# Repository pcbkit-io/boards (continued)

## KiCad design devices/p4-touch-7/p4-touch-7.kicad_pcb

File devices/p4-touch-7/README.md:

# p4-touch-7 — a 7" ESP32-P4 touch screen running NucleoOS

A board for [NucleoOS-P4](https://github.com/indecenti/NucleoOS-P4) (by indecenti): the
Guition JC1060P470C's circuit (its published schematic) at NucleoOS's own pin map, laid out by
PCBKit behind a 7" 1024 × 600 MIPI-DSI touch panel. In the app it runs NucleoOS's own release,
unmodified: the factory image from its GitHub release, booted by Espressif's ESP32-P4 boot ROM on
PCBKit's model of the chip, the card in the microSD socket holding the release's SD-card archive.

| | |
|---|---|
| Processor | ESP32-P4NRW32 (two RISC-V cores at 360 MHz, 32 MB PSRAM in package), W25Q128JV 16 MB flash, 40 MHz crystal |
| Screen | JC1060M070N-I: 7" 1024 × 600 IPS, JD9165 over 2-lane MIPI-DSI (FPC1, 30 pins), GT911 capacitive touch on I2C0 (FPC2, 6 pins); its AVDD from an MT3608, VGH and VGL from charge pumps, the backlight from a second MT3608 dimmed by LEDC (an 18 V zener into its FB holds the output near 19 V with the panel unplugged, under the 30 V its switch pin takes) |
| Radio | ESP32-C6-MINI-1 on the P4's second SD/MMC slot (ESP-Hosted), its antenna over the top edge |
| Audio | ES8311 codec (electret microphone in, PAM8403 to a speaker connector) on I2S0 and I2C0 |
| Storage | microSD socket on SD/MMC slot 0 (GPIO39–44, 4-bit) |
| Clock | DS3231 with a CR2032 |
| USB | three USB-C: the console (CH340C, auto-reset into the boot loader), the P4's full-speed and high-speed ports (the last one a Type-C host: 56 kΩ Rp on CC, 5 V to what is plugged in through an SY6280 switch limited to 750 mA) |
| Power | a Li-ion cell on IP5306 (charger and 5 V boost, its key the power button), SY8089 bucks to 3.3 V and to the P4's 1.2 V core supply |
| Board | 160 × 96 mm, 6 layers (JLCPCB JLC06161H-3313, controlled impedance), four M3 holes onto the panel's standoffs |

<!-- STATUS -->
**Board status** (measured on the dev host with PCBKit's CLI): `pcbkit check`: complete — 0 errors,
23 warnings (the DSI and USB pairs' coupling, impedance and skew where they leave the P4's 0.35 mm
pins, 13 narrower tracks in a class, two rail names, two VSYS stubs the router leaves), 0 unrouted
nets. 179 components, 118 nets, 2644 track segments (6155 mm), 596 vias.
`analysis.run { lens: "ready" }`: 12 to fix (decoupling capacitors 3–4 mm from their P4 supply pins,
under the chip on the back) and 24 to consider.
Every assembled line has its LCSC code (chosen by stock at JLCPCB, 2026-10-25); `pcbkit export
--format fab` succeeds without `--force`. **Two parts are out of stock at JLCPCB**: the ESP32-P4NRW32
(no ESP32-P4 of any revision is; send it as a consigned part) and the 4.2 x 3.2 mm BOOT and RESET
buttons (PTS810, or any 4.2 x 3.2 mm tact switch). The ESP32-C6 is the MINI-1-H4 (the N4's 105 °C
twin, same pins).
<!-- /STATUS -->

## Run it in the browser

Open the board and press **Run**: the page fetches NucleoOS's release (its factory image and its
SD-card archive, from GitHub, checked against the SHA-256 this design declares) and Espressif's ROM,
and runs them. NucleoOS boots to its setup wizard; touch the screen in 3D to go through it to the
launcher.

What does not run, as NucleoOS itself reports it:

- **No radio.** The ESP32-C6 is on the board but held in reset: its own firmware (ESP-Hosted) does
  not run here, so NucleoOS finds no Wi-Fi ("This board has no Wi-Fi radio") and no Bluetooth.
  Nothing pretends to be a network.
- **The RTC.** NucleoOS looks for an RX8130 at 0x14; this board (like Guition's, which fits an
  RX-8025T) has a DS3231 at 0x68, so the clock starts unset.
- The PPA's blender and YUV modes, the JPEG codec and the camera are not modelled yet: an app that
  uses them stops the device and says which block.

## Order, flash

1. Order with assembly (`pcbkit export --format fab`); the panel plugs into FPC1 and FPC2.
2. Flash NucleoOS's factory image over the console port: `esptool.py --chip esp32p4 write_flash 0
   nucleoos-p4-1.2.189-jc1060p470c-factory.bin` (the CH340C's DTR and RTS put the P4 into its boot
   loader); unzip `nucleoos-p4-sdcard.zip` onto a FAT32 microSD card.

NucleoOS's chip revision: its v1.2.x images are built for ESP32-P4 revision v1.x (the image says
"max chip rev v1.99"); new ESP32-P4NRW32X parts are revision v3 and need an image built for it.

Licence: the board CC0 1.0; NucleoOS is the PolyForm Noncommercial License 1.0.0, fetched from its
own release and never copied here.

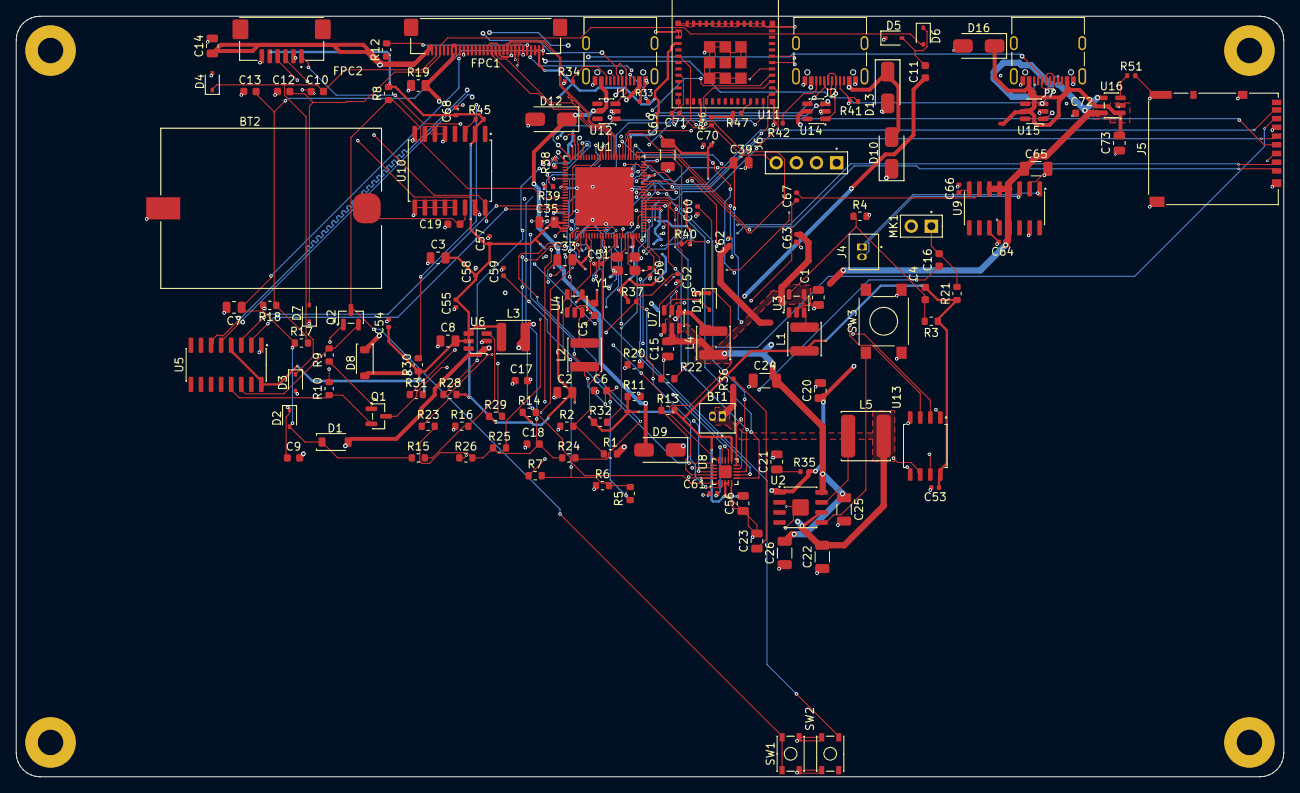
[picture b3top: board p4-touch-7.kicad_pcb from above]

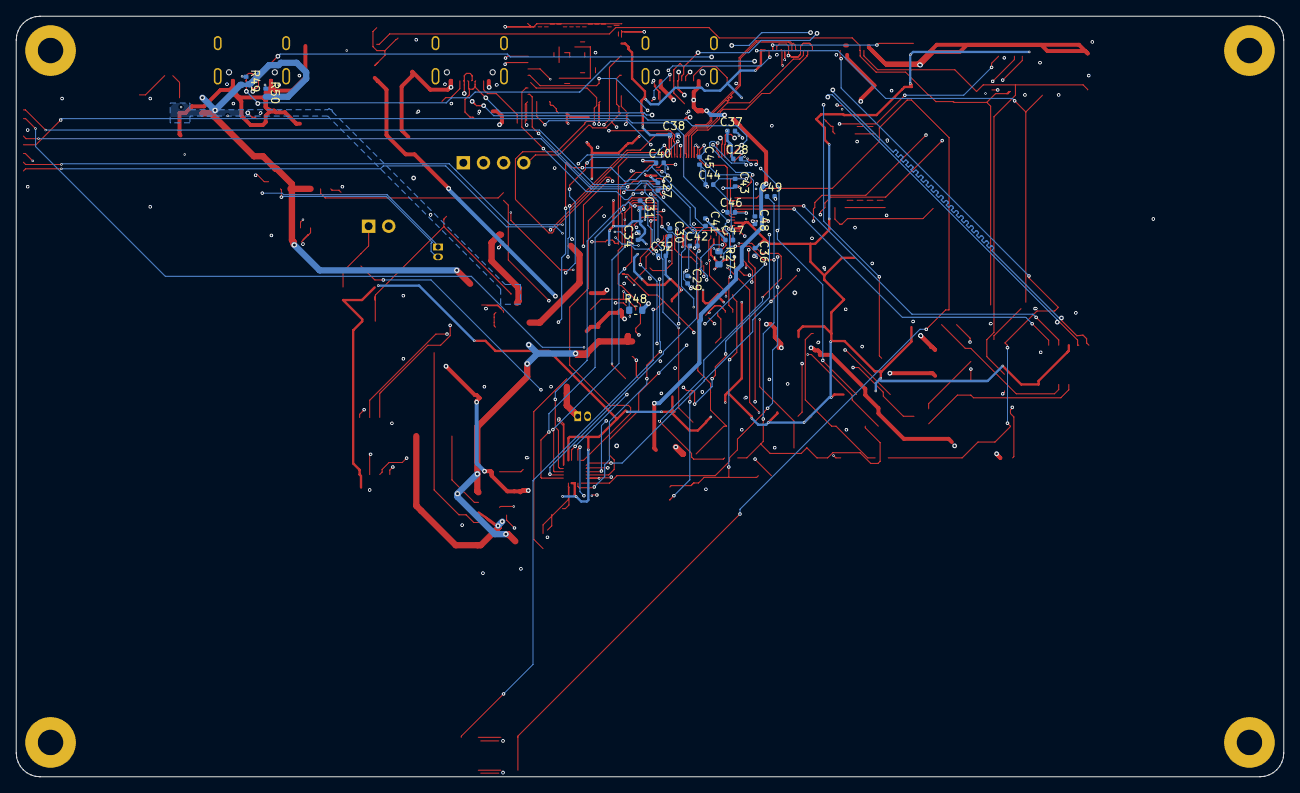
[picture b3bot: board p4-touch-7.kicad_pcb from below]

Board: 6 copper layers, 160.0 x 96.0 mm, 179 parts (25 on the bottom side), 116 nets.

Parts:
BT1: MX1.25-2P; Conn_WireToBoard_1x02_P1.25mm_THT_Vertical
BT2: BS-08-B2AA001; BatteryHolder_MYOUNG_BS-08_CR2032_SMD
C1, C2, C3: 22uF; C_0805_2012Metric
C4: 22pF; C_0603_1608Metric
C5, C6, C18: 10uF; C_0603_1608Metric
C7, C8, C15, C20, C21, C23, C33, C35, C39, C56, C73: 10uF; C_0805_2012Metric
C9, C11, C19: 100nF; C_0603_1608Metric
C10, C12, C13, C16, C17, C72: 1uF; C_0603_1608Metric
C14: 4.7uF; C_0805_2012Metric
C22, C24, C25, C26, C65, C69: 22uF; C_1206_3216Metric
C27, C28, C29, C30, C31, C32, C34, C36, C37, C38, C40, C41, C42, C43, C44, C45, C53, C54, C55, C57, C68, C70: 100nF; C_0402_1005Metric
C46, C47, C48, C49, C52, C58, C59, C60, C61, C62, C63, C64, C66, C71: 1uF; C_0402_1005Metric
C50, C51: 15pF; C_0402_1005Metric
C67: 470nF; C_0402_1005Metric
D1, D8: schottky; D_SOD-123
D2, D3, D5, D6: schottky; D_SOD-323
D4, D15: zener 18V; D_SOD-323
D7: zener 6.8V; D_SOD-323
D9, D10: schottky; D_SMA
D12, D13, D16: tvs 5V; D_SMA
FPC1: FH12-30S-0.5SH(55); Conn_FFC-FPC_1x30_P0.50mm_Horizontal
FPC2: FH12-6S-1SH(55); Conn_FFC-FPC_1x06_P1.00mm_Horizontal
H1, H2, H3, H4: MountingHole_3.2mm_M3_Pad
J1, J2, J7: USB4105-GF-A; USB_C_Receptacle_USB2.0_16P
J4: MX1.25-2P; Conn_WireToBoard_1x02_P1.25mm_THT_Vertical
J5: DM3AT-SF-PEJM5; Hirose_DM3AT_microSD_socket_push-push
J6: PinHeader_1x04_P2.54mm_Vertical
L1, L2: 2.2uH; L_Power_4x4mm
L3, L4: 10uH; L_Power_4x4mm
L5: 1uH; L_Power_6x6mm
LCD1: touch-display; JC1060M070N-I
MK1: CMEJ-0627-42-P; PinHeader_1x02_P2.54mm_Vertical
Q1, Q2: MMBT3904-7-F; SOT-23
R1: 68kohm; R_0603_1608Metric
R2, R4: 100kohm; R_0603_1608Metric
R3: 453kohm; R_0603_1608Metric
R5, R6: 499kohm; R_0603_1608Metric
R7: 0uohm; R_0603_1608Metric
R8, R9, R10, R11, R12, R16, R18, R20, R22, R23, R24, R25, R26, R27: 10kohm; R_0603_1608Metric
R13, R14: 5.1kohm; R_0603_1608Metric
R15: 150kohm; R_0603_1608Metric
R17: 15kohm; R_0603_1608Metric
R19: 3.3ohm; R_0805_2012Metric
R21: 2.2kohm; R_0603_1608Metric
R28, R29, R30, R31, R32: 51kohm; R_0603_1608Metric
R33, R34, R41, R42: 5.1kohm; R_0402_1005Metric
R35, R36: 2ohm; R_0402_1005Metric
R37, R40, R45, R46, R47: 10kohm; R_0402_1005Metric
R38, R39: 2kohm; R_0402_1005Metric
R48: 1kohm; R_0603_1608Metric
R49, R50: 56kohm; R_0402_1005Metric
R51: 9.1kohm; R_0402_1005Metric
SW1, SW2: PTS810SJM250SMTR LFS; SW_Tactile_SPST_4.2x3.2mm_SMD
SW3: PTS645SM43SMTR92 LFS; SW_Tactile_SPST_6x6mm_SMD
U1: ESP32-P4NRW32; QFN-104_10x10mm_0.35mm_pitch_7.5mm_exposed_pad
U2: IP5306; SOIC-8-1EP_3.9x4.9mm_P1.27mm_EP2.09x2.09mm
U3, U4: SY8089AAAC; SOT-23-5
U5: CH340C; SOIC-16_3.9x9.9mm_P1.27mm
U6, U7: MT3608; SOT-23-6
U8: ES8311; QFN-20-1EP_3x3mm_P0.4mm_EP1.65x1.65mm
U9: PAM8403DR; SOIC-16_3.9x9.9mm_P1.27mm
U10: DS3231SN#; SOIC-16W_7.5x10.3mm_P1.27mm
U11: ESP32-C6-MINI-1-N4; ESP32-C6-MINI-1_module_13.2x16.6mm_LGA_53_pads
U12, U14, U15: USBLC6-2SC6; SOT-23-6
U13: W25Q128JVSIQ; SOIC-8_5.23x5.28mm_P1.27mm
U16: SY6280AAC; SOT-23-5
Y1: 40MHz 10pF; Crystal_SMD_3225-4Pin

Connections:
AVDD: C7.1 (a), D1.1 (K), D2.2 (A), FPC1.22, R15.2 (b), R17.2 (b)
AVDD_FB: R15.1 (a), R16.1 (a), U6.3 (FB)
BAT_SENSE: R1.2 (b), R2.1 (a), U1.95 (GPIO52)
BL_FB: D15.2 (A), R48.1 (a), U7.3 (FB)
BL_SW: D8.2 (A), L4.1 (a), U7.1 (SW)
BOOT: Q2.3 (C), R8.1 (a), SW1.1 (a), U1.66 (GPIO35)
C6_CLK: U1.19 (GPIO18), U11.25 (IO19)
C6_CMD: R28.2 (b), U1.20 (GPIO19), U11.24 (IO18)
C6_D0: R29.1 (a), U1.15 (GPIO14), U11.26 (IO20)
C6_D1: R30.2 (b), U1.16 (GPIO15), U11.27 (IO21)
C6_D2: R31.2 (b), U1.17 (GPIO16), U11.28 (IO22)
C6_D3: R32.1 (a), U1.18 (GPIO17), U11.29 (IO23)
C6_EN: C71.1 (a), J6.4, R46.1 (a), U1.98 (GPIO54), U11.8 (EN)
C6_IO2: U1.6 (GPIO6), U11.5 (IO2)
C6_RX: J6.3, U11.30 (RXD0)
C6_TX: J6.2, U11.31 (TXD0)
CHIP_PU: C52.1 (a), Q1.3 (C), R37.1 (a), SW2.1 (a), U1.103 (CHIP_PU)
DAC_P: C67.2 (b), U8.12 (OUTP)
DSI_CLK_N: FPC1.13, U1.37 (DSI_CLKN)
DSI_CLK_P: FPC1.14, U1.38 (DSI_CLKP)
DSI_D0_N: FPC1.7, U1.40 (DSI_DATAN0)
DSI_D0_P: FPC1.8, U1.39 (DSI_DATAP0)
DSI_D1_N: FPC1.10, U1.36 (DSI_DATAN1)
DSI_D1_P: FPC1.11, U1.35 (DSI_DATAP1)
DTR: Q1.2 (E), R10.2 (b), U5.13 (DTR_N)
EN_DCDC: U1.79 (EN_DCDC), U4.1 (EN)
FB_DCDC: R7.2 (b), U1.78 (FB_DCDC)
FS_DN: J2.A7 (DN), J2.B7 (DN), U1.52 (GPIO24), U14.3 (IO2)
FS_DP: J2.A6 (DP), J2.B6 (DP), U1.53 (GPIO25), U14.1 (IO1)
GND: BT1.2, BT2.2 (GND), C1.2 (b), C2.2 (b), C3.2 (b), C5.2 (b), C6.2 (b), C7.2 (b), C8.2 (b), C10.2 (b), C12.2 (b), C13.2 (b), C14.2 (b), C15.2 (b), C17.2 (b), C18.2 (b), C19.2 (b), C20.2 (b), C21.2 (b), C22.2 (b), C23.2 (b), C24.2 (b), C25.2 (b), C26.2 (b), C27.2 (b), C28.2 (b), C29.2 (b), C30.2 (b), C31.2 (b), C32.2 (b), C33.2 (b), C34.2 (b), C35.2 (b), C36.2 (b), C37.2 (b), C38.2 (b), C39.2 (b), C40.2 (b), C41.2 (b), C42.2 (b), C43.2 (b), C44.2 (b), C45.2 (b), C46.2 (b), C47.2 (b), C48.2 (b), C49.2 (b), C50.2 (b), C51.2 (b), C52.2 (b), C53.2 (b), C54.2 (b), C55.2 (b), C56.2 (b), C57.2 (b), C58.2 (b), C59.2 (b), C60.2 (b), C61.2 (b), C62.2 (b), C63.2 (b), C64.2 (b), C65.2 (b), C66.2 (b), C68.2 (b), C69.2 (b), C70.2 (b), C71.2 (b), C72.2 (b), C73.2 (b), D4.2 (A), D5.1 (K), D7.1 (K), D12.2 (A), D13.2 (A), D16.2 (A), FPC1.6, FPC1.9, FPC1.12, FPC1.15, FPC1.21, FPC2.6, H1.1, H2.1, H3.1, H4.1, J1.A1 (GND), J1.A12, J1.B1 (GND), J1.B12, J1.S1 (SHIELD), J2.A1 (GND), J2.A12, J2.B1 (GND), J2.B12, J2.S1 (SHIELD), J5.6 (VSS), J5.SH, J6.1, J7.A1 (GND), J7.A12, J7.B1 (GND), J7.B12, J7.S1 (SHIELD), MK1.2, R2.2 (b), R4.2 (b), R6.2 (b), R16.2 (b), R18.2 (b), R19.2 (b), R20.2 (b), R22.2 (b), R33.2 (b), R34.2 (b), R38.2 (b), R39.2 (b), R41.2 (b), R42.2 (b), R51.2 (b), SW1.2 (b), SW2.2 (b), SW3.2 (b), U1.105 (GND), U2.9 (GND), U3.2 (GND), U4.2 (GND), U5.1 (GND), U6.2 (GND), U7.2 (GND), U8.5 (DGND), U8.10 (AGND), U8.20 (CE), U9.2 (PGND), U9.11 (GND), U9.15 (PGND), U10.5 (GND), U10.6 (GND), U10.7 (GND), U10.8 (GND), U10.9 (GND), U10.10 (GND), U10.11 (GND), U10.12 (GND), U10.13 (GND), U11.1 (GND), U11.2 (GND), U11.11 (GND), U11.14 (GND), U11.36 (GND), U11.37 (GND), U11.38 (GND), U11.39 (GND), U11.40 (GND), U11.41 (GND), U11.42 (GND), U11.43 (GND), U11.44 (GND), U11.45 (GND), U11.46 (GND), U11.47 (GND), U11.48 (GND), U11.49 (GND), U11.50 (GND), U11.51 (GND), U11.52 (GND), U11.53 (GND), U12.2 (GND), U13.4 (GND), U14.2 (GND), U15.2 (GND), U16.2 (GND), Y1.2 (GND), Y1.4 (GND)
HS_DN: J7.A7 (DN), J7.B7 (DN), U1.49 (USB_DM), U15.3 (IO2)
HS_DP: J7.A6 (DP), J7.B6 (DP), U1.50 (USB_DP), U15.1 (IO1)
I2S_DIN: U1.90 (GPIO48), U8.7 (ASDOUT)
I2S_DOUT: U1.10 (GPIO9), U8.9 (DSDIN)
I2S_LRCK: U1.11 (GPIO10), U8.8 (LRCK)
I2S_MCLK: U1.14 (GPIO13), U8.2 (MCLK)
I2S_SCLK: U1.13 (GPIO12), U8.6 (SCLK)
J1/power/cc1: J1.A5 (CC1), R33.1 (a)
J1/power/cc2: J1.B5 (CC2), R34.1 (a)
J2/power/cc1: J2.A5 (CC1), R41.1 (a)
J2/power/cc2: J2.B5 (CC2), R42.1 (a)
J3/cc1: J7.A5 (CC1), R49.1 (a)
J3/cc2: J7.B5 (CC2), R50.1 (a)
J3/iset: R51.1 (a), U16.3 (ISET)
KEY: SW3.1 (a), U2.5 (KEY)
LCD_PWM: R20.1 (a), U1.25 (GPIO23), U7.4 (EN)
LCD_RST: FPC1.4, R11.1 (a), U1.5 (GPIO5)
LCD_STBY: FPC1.5, R12.2 (b)
LCD_SW: C9.2 (b), C11.2 (b), D1.2 (A), L3.1 (a), U6.1 (SW)
LEDA: C14.1 (a), D8.1 (K), D15.1 (K), FPC1.29, FPC1.30
LEDK: FPC1.23, FPC1.24, R19.1 (a), R48.2 (b)
MIC_BIAS: C16.1 (a), MK1.1, R21.1 (a)
MIC_N: C17.1 (a), U8.17 (MIC1N)
MIC_P: C16.2 (b), U8.18 (MIC1P)
unnamed: C43.1 (a), C44.1 (a), C47.1 (a), U1.59 (VDD_PSRAM_0), U1.67 (VDD_PSRAM_1), U1.72 (VDDO_PSRAM)
unnamed: C45.1 (a), C48.1 (a), U1.41 (VDD_MIPI_DPHY), U1.73 (VDDO_3)
unnamed: C46.1 (a), U1.71 (VDDO_FLASH)
unnamed: C50.1 (a), U1.100 (XTAL_P), Y1.1 (X1)
unnamed: C51.1 (a), U1.99 (XTAL_N), Y1.3 (X2)
unnamed: C59.1 (a), U8.16 (VMID)
unnamed: C60.1 (a), U8.15 (ADCVREF)
unnamed: C61.1 (a), U8.14 (DACVREF)
unnamed: C66.1 (a), U9.8 (VREF)
unnamed: C67.1 (a), U9.7 (INL)
unnamed: L1.1 (a), U3.3 (LX)
unnamed: L2.1 (a), U4.3 (LX)
unnamed: L5.2 (b), U2.7 (SW)
unnamed: R38.1 (a), U1.34 (DSI_REXT)
unnamed: R39.1 (a), U1.48 (CSI_REXT)
unnamed: R40.2 (b), U1.27 (FLASH_CS), U13.1 (nCS)
unnamed: R45.1 (a), U10.3 (INT_SQW)
unnamed: R47.1 (a), U11.22 (IO8)
unnamed: U1.28 (FLASH_Q), U13.2 (DO)
unnamed: U1.29 (FLASH_WP), U13.3 (nWP)
unnamed: U1.31 (FLASH_HOLD), U13.7 (nHOLD)
unnamed: U1.32 (FLASH_CK), U13.6 (CLK)
unnamed: U1.33 (FLASH_D), U13.5 (DI)
PA_EN: R22.1 (a), U1.12 (GPIO11), U9.12 (SHDN)
PUMP_H: C9.1 (a), D2.1 (K), D3.2 (A)
PUMP_L: C11.1 (a), D5.2 (A), D6.1 (K)
Q1B: Q1.1 (B), R9.2 (b)
Q2B: Q2.1 (B), R10.1 (a)
RTC_BAT: BT2.1 (VBAT), C19.1 (a), U10.14 (VBAT)
RTS: Q2.2 (E), R9.1 (a), U5.14 (RTS_N)
RXD0: U1.70 (GPIO38), U5.2 (TXD)
SCL: FPC2.3, R14.1 (a), U1.8 (GPIO8), U8.1 (CCLK), U10.16 (SCL)
SDA: FPC2.4, R13.2 (b), U1.7 (GPIO7), U8.19 (CDATA), U10.15 (SDA)
SD_CLK: J5.5 (CLK), U1.84 (GPIO43)
SD_CMD: J5.3 (CMD), R23.2 (b), U1.86 (GPIO44)
SD_D0: J5.7 (DAT0), R24.1 (a), U1.80 (GPIO39)
SD_D1: J5.8 (DAT1), R25.1 (a), U1.81 (GPIO40)
SD_D2: J5.1 (DAT2), R26.2 (b), U1.82 (GPIO41)
SD_D3: J5.2 (CD_DAT3), R27.1 (a), U1.83 (GPIO42)
SD_VDD: C18.1 (a), C49.1 (a), J5.4 (VDD), R23.1 (a), R24.2 (b), R25.2 (b), R26.1 (a), R27.2 (b), U1.74 (VDDO_4)
SPK_N: J4.2, U9.3 (OUTLN)
SPK_P: J4.1, U9.1 (OUTLP)
TP_INT: FPC2.1, U1.23 (GPIO21)
TP_RST: FPC2.2, U1.24 (GPIO22)
TTL_DN: J1.A7 (DN), J1.B7 (DN), U5.6 (UDN), U12.3 (IO2)
TTL_DP: J1.A6 (DP), J1.B6 (DP), U5.5 (UDP), U12.1 (IO1)
TXD0: U1.69 (GPIO37), U5.3 (RXD)
U2Support/C6_P: C21.1 (a), R35.1 (a)
U2Support/C7_P: C23.1 (a), R36.2 (b)
V3: C2.1 (a), C3.1 (a), C4.1 (a), C5.1 (a), C8.1 (a), C27.1 (a), C28.1 (a), C29.1 (a), C30.1 (a), C31.1 (a), C32.1 (a), C33.1 (a), C34.1 (a), C35.1 (a), C36.1 (a), C37.1 (a), C38.1 (a), C53.1 (a), C54.1 (a), C55.1 (a), C56.1 (a), C57.1 (a), C58.1 (a), C68.1 (a), C69.1 (a), C70.1 (a), FPC1.2, FPC1.3, FPC2.5, L1.2 (b), L3.2 (b), R3.1 (a), R8.2 (b), R11.2 (b), R12.1 (a), R13.1 (a), R14.2 (b), R21.2 (b), R28.1 (a), R29.2 (b), R30.1 (a), R31.1 (a), R32.2 (b), R37.2 (b), R40.1 (a), R45.2 (b), R46.2 (b), R47.2 (b), U1.9 (VDD_LP), U1.21 (VDD_IO_0), U1.30 (VDD_FLASHIO), U1.51 (VDD_USBPHY), U1.62 (VDD_IO_4), U1.75 (VDD_LDO), U1.77 (VDD_DCDCC), U1.85 (VDD_IO_5), U1.96 (VDD_IO_6), U1.101 (VDD_ANA), U1.102 (VDD_BAT), U4.4 (IN), U5.4 (V3), U5.16 (VCC), U6.4 (EN), U6.5 (VIN), U8.3 (PVDD), U8.4 (DVDD), U8.11 (AVDD), U10.2 (VCC), U11.3 (P3V3), U13.8 (VCC)
V3_FB: C4.2 (b), R3.2 (b), R4.1 (a), U3.5 (FB)
VBAT: BT1.1, C22.1 (a), L5.1 (a), R1.1 (a), R36.1 (a), U2.6 (BAT)
VBUS: C20.1 (a), D9.1 (K), D10.1 (K), R35.2 (b), U2.1 (VIN)
VBUS_FS: D10.2 (A), D13.1 (K), J2.A4 (VBUS), J2.A9, J2.B4 (VBUS), J2.B9, U14.5 (VBUS)
VBUS_HOST: C73.1 (a), D16.1 (K), J7.A4 (VBUS), J7.A9, J7.B4 (VBUS), J7.B9, U15.5 (VBUS), U16.1 (OUT)
VBUS_TTL: D9.2 (A), D12.1 (K), J1.A4 (VBUS), J1.A9, J1.B4 (VBUS), J1.B9, U12.5 (VBUS)
VCOM: C13.1 (a), FPC1.1, R17.1 (a), R18.1 (a)
VGH: C10.1 (a), D3.1 (K), D4.1 (K), FPC1.28
VGL: C12.1 (a), D6.2 (A), D7.2 (A), FPC1.27
VHP: C6.1 (a), C39.1 (a), C40.1 (a), C41.1 (a), C42.1 (a), L2.2 (b), R5.2 (b), U1.26 (VDD_HP_0), U1.76 (VDD_HP_2), U1.91 (VDD_HP_3)
VHP_FB: R5.1 (a), R6.1 (a), R7.1 (a), U4.5 (FB)
VSYS: C1.1 (a), C15.1 (a), C24.1 (a), C25.1 (a), C26.1 (a), C62.1 (a), C63.1 (a), C64.1 (a), C65.1 (a), C72.1 (a), L4.2 (b), R49.2 (b), R50.2 (b), U2.8 (VOUT), U3.1 (EN), U3.4 (IN), U7.5 (VIN), U9.4 (PVDD), U9.5 (MUTE), U9.6 (VDD), U9.13 (PVDD), U16.4 (EN), U16.5 (IN)

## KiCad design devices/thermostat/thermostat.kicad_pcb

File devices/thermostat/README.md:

# thermostat — a 24 V AC wall thermostat on an ESP32

A thermostat for a furnace and an air conditioner on the usual four-wire hookup (R, C, W, Y, G): an
ESP32-WROOM-32E reads the room from an SHT40 every two seconds and calls heat (W), cooling (Y) and
the fan (G) through three relays, with 0.5 °C of hysteresis either side of the set point. A 0.96"
OLED shows the temperature large, the set point, the mode, the humidity and the calls; three
buttons set them. It takes its power from the furnace's own transformer (R and C).

| | |
|---|---|
| Processor | ESP32-WROOM-32E-N4 (two Xtensa LX6 cores, 4 MB flash); RESET and BOOT buttons |
| Sensor | SHT40-AD1B at 0x44 on I2C0 (GPIO21 SDA, GPIO22 SCL), at the bottom edge, away from the regulators |
| Display | 0.96" 128 × 64 SSD1306 OLED module at 0x3C on the same bus, on a 4-pin socket |
| Buttons | UP GPIO32, DOWN GPIO33, MODE GPIO25 (to ground, internal pull-ups); MODE cycles OFF / HEAT / COOL / AUTO, UP and DOWN move the set point by 0.5 °C (10–30 °C) |
| Calls | GPIO26 (W), GPIO27 (Y), GPIO14 (G) → ULN2003A → three SRD-05VDC-SL-C relays connecting R to W, Y, G |
| Power | J1: R, C (24 V AC) → bridge (4 × US1M) → SMBJ36A → LMR38020 buck (80 V, the standard `Buck` block) to 5 V (relays) → AMS1117-3.3 (logic) |
| Wiring | J1 (R, C) and J3 (W, Y, G): Phoenix MKDS 1,5 terminal blocks, 5.08 mm |
| Programming | J2: GND, TX, RX, EN, IO0 for a 3.3 V USB-serial adapter (115200 baud): hold BOOT, press RESET, `esptool.py write_flash 0x1000 U1.bin` |
| Board | 84 × 76 mm, 2 layers, four M3 holes |

<!-- STATUS -->
**Board status** (measured on the dev host with PCBKit's CLI): `pcbkit check`: complete — 0 errors, 1 warning (erc-rail-name), 0 unrouted nets. 45 components, 29 nets, 280 track segments (934 mm), 30 vias.
`analysis.run { lens: "ready" }`: Typical scenario, partial. Nothing to fix, 2 to consider, 9 ok: weigh the warnings (tell the person about the ones that are their choice), then the board is ready to order.
`pcbkit export --format fab` succeeds without `--force`: every assembled line of the BOM has an LCSC code (JLCPCB assembly).
<!-- /STATUS -->

| Finding | Why |
|---|---|
| J2 is not on an edge | the programming header, used on the bench |
| No test points | the programming header carries the console; the rails are on large parts |
| The buck needs an operating load / thermal parameters / parts not covered | the analysis' own caveats: the board draws under 0.5 W |

The supply: 24 V AC is about 34 V at its peaks after the bridge (up to 40 V on a high line). The
SMBJ36A takes the spikes, clamping them near 58 V; the LMR38020 buck takes 80 V at its input (the
LM2596 this board had took 45 V, under the TVS's clamp).

## Run it in the browser

Open https://app.pcbkit.io/github/pcbkit-io/boards/tree/main/devices/thermostat, open the
Laboratory and press **Build & run**: the page builds `firmware/` for the ESP32 (ESP-IDF's register
headers) and runs it on a model of the chip, its I2C, GPIO and the OLED. `sim/house.js` is the house:
one room that leaks heat to the outside, heated by a 4 kW furnace while W is called and cooled by a
3 kW air conditioner while Y is (the calls read at the relay driver's inputs), its temperature
reaching the SHT40. Controls: the outside temperature, the room at the start, a time lapse, opening
the window. The buttons answer to ↑, ↓ and M.

**Wi-Fi is not here.** The ESP32's radio is not simulated (it is driven by closed libraries; the
model stops a program that turns it on and says so), and this firmware does not use it: it is the
thermostat without a network. Everything else is the program you flash.

## Order, flash, install

1. Order with assembly (JLCPCB: `pcbkit export --format fab`, or `fab.order` in the app); plug the
   OLED module into its socket.
2. Flash through J2 (`pcbkit export --format firmware` gives the image and the esptool command).
3. Turn the furnace's power off; wire R, C, W, Y, G to J1 and J3 as on the old thermostat.

Licence: CC0 1.0.

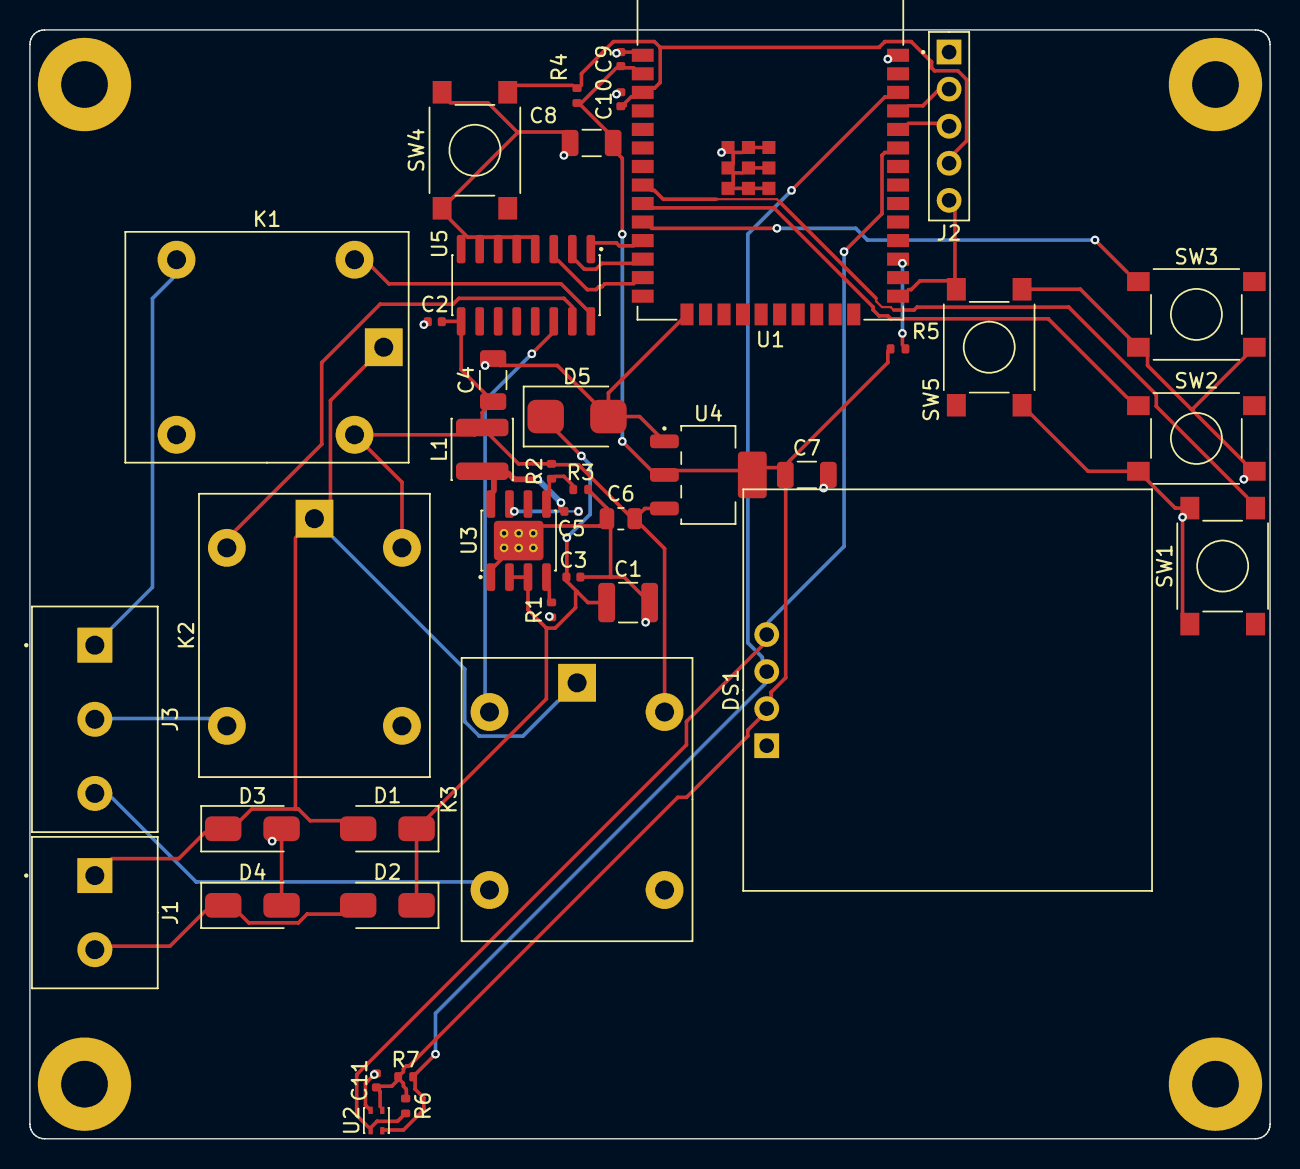
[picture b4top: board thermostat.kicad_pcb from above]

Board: 2 copper layers, 85.0 x 76.0 mm, 45 parts (0 on the bottom side), 29 nets.

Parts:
C1: 10uF; C_1210_3225Metric
C2, C3, C5, C9, C11: 100nF; C_0402_1005Metric
C4, C7, C8: 22uF; C_1206_3216Metric
C6: 10uF; C_0805_2012Metric
C10: 1uF; C_0402_1005Metric
D1, D2, D3, D4: rectifier; D_SMA
D5: tvs 36V; D_SMB
DS1: SSD1306 0.96in 128x64 I2C OLED module; OLED_0.96in_I2C_Socket_1x04_P2.54mm
H1, H2, H3, H4: MountingHole_3.2mm_M3_Pad
J1: 1715721; TerminalBlock_1x02_P5.08mm
J2: PinHeader_1x05_P2.54mm_Vertical
J3: 1715734; TerminalBlock_1x03_P5.08mm
K1, K2, K3: SRD-05VDC-SL-C; Relay_SPDT_Songle_SRD_Form_C
L1: 100uH; L_Power_4x4mm
R1: 52.3kohm; R_0402_1005Metric
R2: 120kohm; R_0402_1005Metric
R3: 30kohm; R_0402_1005Metric
R4, R5, R6, R7: 10kohm; R_0402_1005Metric
SW1, SW2, SW3, SW4, SW5: PTS645SM43SMTR92 LFS; SW_Tactile_SPST_6x6mm_SMD
U1: ESP32-WROOM-32E-N4; ESP32-WROOM-32E_module_18x25.5mm_38_edge_pads_EPAD
U2: SHT40-AD1B-R3; DFN-4_1.5x1.5mm_0.8mm_pitch
U3: LMR38020SDDAR; SOIC-8-1EP_3.9x4.9mm_P1.27mm_EP2.71x3.4mm_ThermalVias
U4: AMS1117-3.3; SOT-223
U5: ULN2003AD; SOIC-16_3.9x9.9mm_P1.27mm

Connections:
BOOT: J2.5, SW5.1 (a), U1.25 (IO0)
C: D2.2 (A), D4.1 (K), J1.2
COOL: U1.12 (IO27), U5.2 (IN2)
DOWN: SW2.1 (a), U1.9 (IO33)
EN: C10.1 (a), J2.4, R4.2 (b), SW4.1 (a), U1.3 (EN)
FAN: U1.13 (IO14), U5.3 (IN3)
G: J3.3, K3.4 (NO)
GND: C1.2 (b), C2.2 (b), C3.2 (b), C4.2 (b), C6.2 (b), C7.2 (b), C8.2 (b), C9.2 (b), C10.2 (b), C11.2 (b), D3.2 (A), D4.2 (A), D5.2 (A), DS1.1 (GND), J2.1, R1.2 (b), R3.2 (b), SW1.2 (b), SW2.2 (b), SW3.2 (b), SW4.2 (b), SW5.2 (b), U1.1 (GND), U1.15 (GND), U1.38 (GND), U1.39 (GND), U2.4 (VSS), U3.1 (GND), U3.9 (GND), U4.1 (GND), U5.4 (IN4), U5.5 (IN5), U5.6 (IN6), U5.7 (IN7), U5.8 (GND)
HEAT: U1.11 (IO26), U5.1 (IN1)
KG: K3.5 (COIL2), U5.14 (OUT3)
KW: K1.5 (COIL2), U5.16 (OUT1)
KY: K2.5 (COIL2), U5.15 (OUT2)
MODE: SW3.1 (a), U1.10 (IO25)
unnamed: R5.1 (a), U1.27 (IO16)
R: D1.2 (A), D3.1 (K), J1.1, K1.1 (COM), K2.1 (COM), K3.1 (COM)
RX: J2.3, U1.34 (RXD0)
SCL: DS1.3 (SCL), R7.2 (b), U1.36 (IO22), U2.2 (SCL)
SDA: DS1.4 (SDA), R6.2 (b), U1.33 (IO21), U2.1 (SDA)
TX: J2.2, U1.35 (TXD0)
UP: SW1.1 (a), U1.8 (IO32)
V3: C7.1 (a), C8.1 (a), C9.1 (a), C11.1 (a), DS1.2 (VCC), R4.1 (a), R5.2 (b), R6.1 (a), R7.1 (a), U1.2 (P3V3), U2.3 (VDD), U4.2 (VOUT), U4.4 (VOUT)
V5: C2.1 (a), C4.1 (a), C6.1 (a), K1.2 (COIL1), K2.2 (COIL1), K3.2 (COIL1), L1.2 (b), R2.2 (b), U4.3 (VIN), U5.9 (COM)
VDC: C1.1 (a), C3.1 (a), D1.1 (K), D2.1 (K), D5.1 (K), U3.2 (EN), U3.3 (IN)
W: J3.1, K1.4 (NO)
Y: J3.2, K2.4 (NO)
buck/bst: C5.1 (a), U3.7 (BST)
buck/fb: R2.1 (a), R3.1 (a), U3.5 (FB)
buck/rt: R1.1 (a), U3.4 (RT)
buck/sw: C5.2 (b), L1.1 (a), U3.8 (SW)

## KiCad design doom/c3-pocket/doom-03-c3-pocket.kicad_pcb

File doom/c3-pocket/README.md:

# 03 · c3-pocket — a Game Boy-shaped RISC-V Doom on an ESP32-C3

A small portrait handheld (52 × 128 mm) around an ESP32-C3-MINI-1 module: one RISC-V core, 400 KB
of SRAM, 4 MB of flash, a 1.3" IPS screen, eight buttons, a piezo and two 18650 cells behind it,
charged from its USB-C port.
The C3 has no PSRAM, so Doom is cut down the way rp2040-doom cut it for the RP2040.

| | |
|---|---|
| Processor | ESP32-C3-MINI-1-H4 (the -N4's 105 °C twin: same pins and 4 MB flash; the -N4 is out of stock at JLCPCB): ESP32-C3, one **RV32IMC** core (Espressif's own, 4-stage pipeline) at 160 MHz, 400 KB SRAM (16 KB of it cache), 384 KB ROM, 4 MB flash in the module (MSPI, XIP through the cache), Wi-Fi/BLE unused |
| Display | 1.3" 240 × 240 IPS, ST7789, SPI without CS (mode 3): GPIO6 SCK, GPIO7 MOSI, GPIO5 D/C, GPIO4 RES; backlight on |
| Input | 8 × 5.1 mm tact switches: d-pad IO0–IO3, fire IO10, use RXD0 (IO20), strafe TXD0 (IO21), menu IO9 (= BOOT: held at reset it enters download mode) |
| Sound | piezo on IO8 (LEDC PWM; IO8 is a strapping pin held high by 10 kΩ, the piezo is DC-open) |
| Power | 2 × 18650 Li-ion in parallel (1S2P, a 2 A resettable fuse per cell) behind reverse-cell (AO3401A) and DW01A + FS8205A protection; BQ24075 charger with power path from USB-C (fuse, TVS); SYS → AP2112K-3.3 LDO, its enable on the slide switch |
| Programming | USB-C to the C3's own USB Serial/JTAG (IO18/IO19): `esptool.py` flashes it, no bridge chip; JTAG debugging over the same cable; RESET on the back, BOOT = MENU |
| Board | 52 × 128 mm, 2 layers, four M3 holes; front: display, buttons, USB-C (left edge, near the top), charger, switch, test pads; back: two 18650 holders, the module (top edge, antenna away from the hand), RESET, piezo |

<!-- STATUS -->
**Board status** (measured on the dev host with PCBKit's CLI): `pcbkit check`: complete — 0 errors, 3 warnings (diff-pair-uncoupled, erc-rail-name), 0 unrouted nets. 60 components, 42 nets, 423 track segments (1466 mm), 54 vias.
`analysis.run { lens: "ready" }`: Typical scenario, partial. Nothing to fix, 3 to consider, 16 ok: weigh the warnings (tell the person about the ones that are their choice), then the board is ready to order.
`pcbkit export --format fab` succeeds without `--force`: every assembled line of the BOM has an LCSC code.
<!-- /STATUS -->

## Run it in the browser

Open https://app.pcbkit.io/github/pcbkit-io/boards/tree/main/doom/c3-pocket, open the
Laboratory and press **Build & run**: the page builds `doom/` for the C3's RV32IMC core (with
rp2040-doom's `DOOM1.WHX` linked into the flash), boots it the way the chip's boot ROM boots an
image from flash, and draws the ST7789's frames on the board. Play with the keyboard (arrows,
F fire, Space use, S held to strafe, M menu; fire confirms in the menus) or a gamepad (`input.js`).

## How Doom fits

`doom/` is rp2040-doom's engine (kilograham, GPL-2: its compressed level format and its
`DOOM1.WHX`, the shareware episode in 1.8 MB) on PCBKit's ESP32-C3 kit instead of ESP-IDF: the
WHX and the constant tables read in place from the flash through the cache, the zone heap in the
DRAM (190 KB of data and bss, 70 KB of heap inside the 256 KiB its 16-bit pointers reach), the CPU
at 160 MHz. Each 320 × 200 frame is scaled by 3/4 into the panel's middle 240 × 150 (of four
columns or lines the middle two averaged), RGB565 over GP-SPI2 at 40 MHz in SPI mode 3 (the
module has no chip select): 72 KB per frame, 14 ms. The eight buttons are read from their GPIOs
(pulled up). The firmware is silent: the piezo is not driven yet.

## Power

| State | Current (estimate) |
|---|---|
| ESP32-C3 at 160 MHz, radio off | 25–30 mA |
| ST7789 1.3" with backlight | 20–30 mA |
| **Total** | **~55 mA at 3.3 V** |

Two 18650 Li-ion cells in Keystone 1042 holders on the back, upright side by side, in parallel
(1S2P, 3.0–4.2 V). From the cells to the module:

- **Reverse cells:** an AO3401A P-MOSFET in the plus line, its gate at the cells' minus: cells put
  in backwards leave it off and the board unpowered (it conducts both ways when they are right, so
  charging goes through it too). One cell reversed against the other is what the **per-cell fuses**
  are for: each holder's + reaches the pack through its own 2 A resettable fuse (Littelfuse
  1812L200/16GR: 16 V, 100 A interrupting), so a cell put in backwards, or one much fuller than
  the other, trips both in milliseconds instead of shorting the two cells together (tens of
  amperes); take the cell out and they reset. Still put each cell's + at the end the silkscreen
  marks.
- **Protection:** DW01A + FS8205A in the pack's minus: over-charge 4.3 V, over-discharge 2.4 V,
  over-current about 3 A and short circuit, for the pack. Flat-top unprotected 18650 cells fit
  the holders.
- **USB-C input:** 5.1 kΩ on CC1 and CC2 (any USB-C charger or computer gives 5 V), a 750 mA
  resettable fuse (nSMD075), a 5 V TVS (SMF5.0A), and a USBLC6-2 ESD array on D+/D−.
- **Charger with power path:** a TI BQ24075 in USB500 mode (at most 500 mA from the port), ISET
  for 800 mA (RISET 1.13 kΩ), RILIM 1.18 kΩ, safety timers off (two cells in parallel charge longer
  than its longest timer; termination is by current), TS tied to 10 kΩ (no thermistor). A linear
  charger passes on at most what it takes in, so from USB the cells charge at up to about 500 mA.
  Its output SYS runs the board from USB when one is plugged in and from the cells otherwise.
- **3.3 V:** the AP2112K-3.3 LDO from SYS (about 25 mV dropout at this board's 55 mA): 3.3 V down
  to about 3.33 V on the cells, then it follows them; the C3 runs to 3.0 V, so the game runs until
  the cells are nearly empty.
- **On/off:** the slide switch on the right edge drives the LDO's enable (1 MΩ pulls it off); the
  charger charges with the switch off; off, the board draws only the charger's and the
  protection's few µA.

Two 3000 mAh cells (about 22 Wh) at ~0.2 W: **about 100 h** of play (estimate). A full charge of
two empty cells from USB at about 500 mA takes about 12 h.

## Charging

Plug any USB-C charger or computer into J1 (the left edge, near the top). The red LED (CHG) is on
while the cells charge and goes out when they are full; the green LED (USB) is on while USB power
is present. The board runs from USB while it charges, switched on or off. Insert the cells with +
at the end the back's silkscreen marks (the top).

## Modules plugged in by hand

The assembly solders a 1x7 female socket for the display; the module is bought separately:

- **DS1: 1.3" 240 × 240 ST7789 IPS module, SPI without CS** (7 pins: GND, VCC, SCL, SDA, RES, DC,
  BLK), its pin header soldered on as it comes, plugged in on the front.

## Check warnings and why they stay

| Warning | Why it is acceptable |
|---|---|
| `diff-pair-uncoupled` and `skew` on DP / DN (a few tens of mm uncoupled, a few mm of skew) | USB 2.0 full speed (12 Mbit/s, 83 ns a bit): the connector is on the front, the C3 on the back; tens of mm uncoupled and 6 mm of skew (about 40 ps) are nothing at this rate |
| `track-width-class` on GND: about 1 mm narrowed to 0.19 mm, at a via beside the LDO and the module's decoupling | a local ground stub between parts packed under the module; it lies inside the ground pours of both sides, which carry the ground current |

## Firmware: build and flash

- **Build:** in PCBKit, the Laboratory's **Build & run** builds `doom/` (RV32IMC, the kit's
  start-up and link layout); then export the firmware (`export.run { format: "firmware" }`):
  `U1.bin`, the whole flash from offset 0 (the boot image the ROM loads, then the program's code
  and constants and the WHX at their pages). No 2nd-stage bootloader or partition table: the ROM
  boots the image directly.
- **Flashing on arrival:** switch the board on and plug its USB-C into a computer: the C3's USB
  Serial/JTAG enumerates (303a:1001, `/dev/ttyACM0` or a COM port) even with the module's flash
  blank, and `esptool` resets the chip into its ROM download mode through it by itself:
  `esptool.py --chip esp32c3 -p /dev/ttyACM0 write_flash 0x0 U1.bin` (or the browser's ESP Web
  Flasher at offset 0). If a running program has taken the USB pins over: hold MENU (IO9, the
  C3's BOOT strap) and press RESET on the back: ROM download mode, then flash as above. Press
  RESET: Doom starts.

## Bill of materials

Rough cost at 10 pieces (estimates): ESP32-C3-MINI-1 $2.20 · ST7789 1.3" module $3.00 · AP2112K $0.15 · USB-C + ESD $0.40 · buttons $0.30 · piezo $0.30 · switch
$0.10 · two 18650 holders $9.80 · BQ24075 and protection $1.30 · PCB $2.00 → **about $22** without the cells.

<!-- BOM -->
The assembly BOM as `pcbkit export --format fab` writes it (JLCPCB assembly: LCSC codes; the modules' lines are their sockets):

| Qty | Refs | Part | LCSC | Footprint |
|---|---|---|---|---|
| 2 | BT1, BT2 | 1042 | C5249310 | BatteryHolder_Keystone_1042_1x18650 |
| 1 | BZ1 | GPC12075YB-5V4000 | C252948 | Buzzer_D12.0mm_H7.5mm_P6.50mm |
| 1 | C1 | 10uF | C15850 | C_0805_2012Metric |
| 2 | C2, C6 | 100nF | C1525 | C_0402_1005Metric |
| 3 | C3, C7, C8 | 1uF | C52923 | C_0402_1005Metric |
| 1 | D1 | tvs 5V | C284108 | D_SOD-123 |
| 1 | DS1 | MSP1308 1.3in 240x240 IPS SPI module (ST7789) | C2932672 | TFT_1.3in_ST7789_Socket_1x07_P2.54mm |
| 1 | F1 | PTC 750mA | C70078 | Fuse_1206_3216Metric |
| 2 | F2, F3 | PTC 2000mA | C18198340 | Fuse_1812_4532Metric |
| 1 | J1 | USB4105-GF-A | C165948 | USB_C_Receptacle_USB2.0_16P |
| 1 | Q1 | AO3401A | C15127 | SOT-23 |
| 1 | Q2 | FS8205A | C5148694 | TSSOP-8_4.4x2.93mm_P0.65mm |
| 1 | R1 | 1Mohm | C26083 | R_0402_1005Metric |
| 4 | R2, R3, R4, rTs | 10kohm | C25744 | R_0402_1005Metric |
| 2 | R5, R6 | 5.1kohm | C25905 | R_0402_1005Metric |
| 1 | R7 | 100kohm | C25741 | R_0402_1005Metric |
| 1 | R9 | 100ohm | C25076 | R_0402_1005Metric |
| 1 | R10 | 1kohm | C11702 | R_0402_1005Metric |
| 8 | SW1, SW2, SW3, SW4, SW5, SW6, SW7, SW8 | TS-1187A-B-A-B | C318884 | SW_Tactile_SPST_5.1x5.1mm_SMD |
| 1 | SW9 | MSK12C02 | C431540 | SW_Slide_SPDT_Shouhan_MSK12C02 |
| 1 | SW10 | PTS645SM43SMTR92 LFS | C221880 | SW_Tactile_SPST_6x6mm_SMD |
| 1 | U1 | ESP32-C3-MINI-1-H4 | C2934569 | ESP32-C3-MINI-1_module_13.2x16.6mm_LGA_53_pads |
| 1 | U2 | BQ24075RGTR | C15464 | QFN-16-1EP_3x3mm_P0.5mm_EP1.68x1.68mm |
| 1 | U3 | DW01A | C351410 | SOT-6_1.6x2.9mm_P0.95mm |
| 1 | U4 | AP2112K-3.3TRG1 | C51118 | SOT-23-5 |
| 1 | U5 | USBLC6-2SC6 | C7519 | SOT-23-6 |
| 2 | cBat, cSys | 4.7uF | C1779 | C_0805_2012Metric |
| 1 | cIn | 1uF | C15849 | C_0603_1608Metric |
| 1 | ledChg | red | C2286 | LED_0603_1608Metric |
| 1 | ledPg | green | C12624 | LED_0603_1608Metric |
| 2 | rChg, rPg | 1.5kohm | C25867 | R_0402_1005Metric |
| 1 | rIlim | 1.18kohm | C270651 | R_0402_1005Metric |
| 1 | rIset | 1.13kohm | C67014 | R_0402_1005Metric |
<!-- /BOM -->

## What PCBKit's simulation models

The ESP32-C3 as its boot ROM leaves it after a flash boot (the image checked and loaded), the
BBPLL and the CPU clock with their rules, the watchdogs, the cache's MMU, IO_MUX and the GPIO
matrix's outputs, SYSTIMER and its interrupt through the interrupt matrix, GP-SPI2; the ST7789
(command set, addressing, a module without chip select); the buttons. The same image boots through
the chip's own ROM in Espressif's QEMU. Not modelled: GDMA, LEDC (the game is silent, as this
firmware is), USB Serial/JTAG, the radio, cache timing, the cells and the charger.

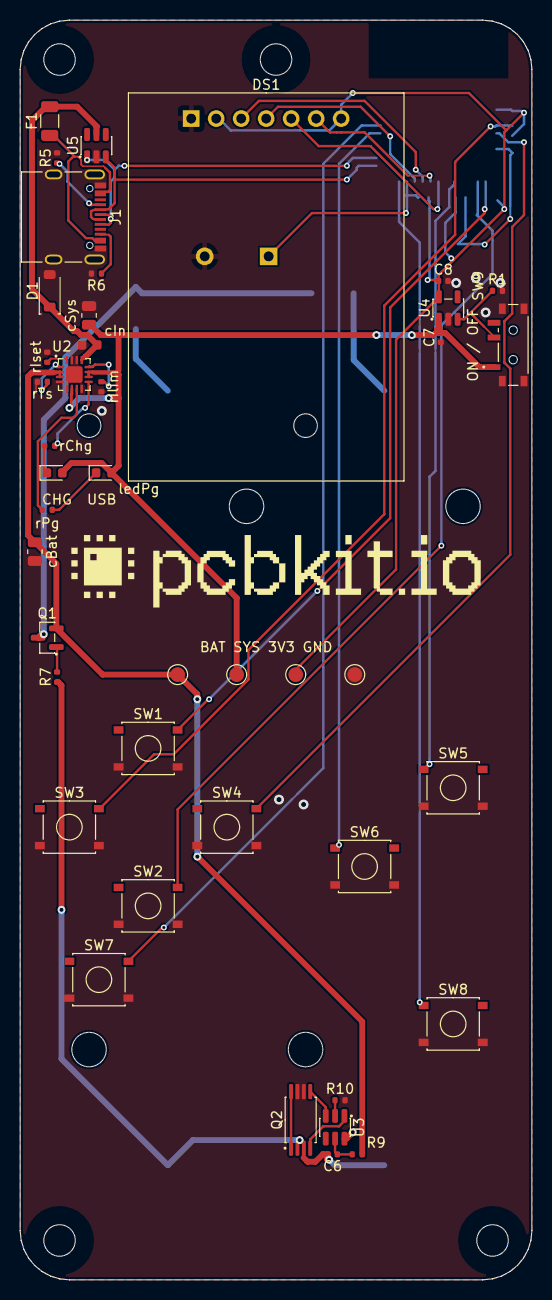
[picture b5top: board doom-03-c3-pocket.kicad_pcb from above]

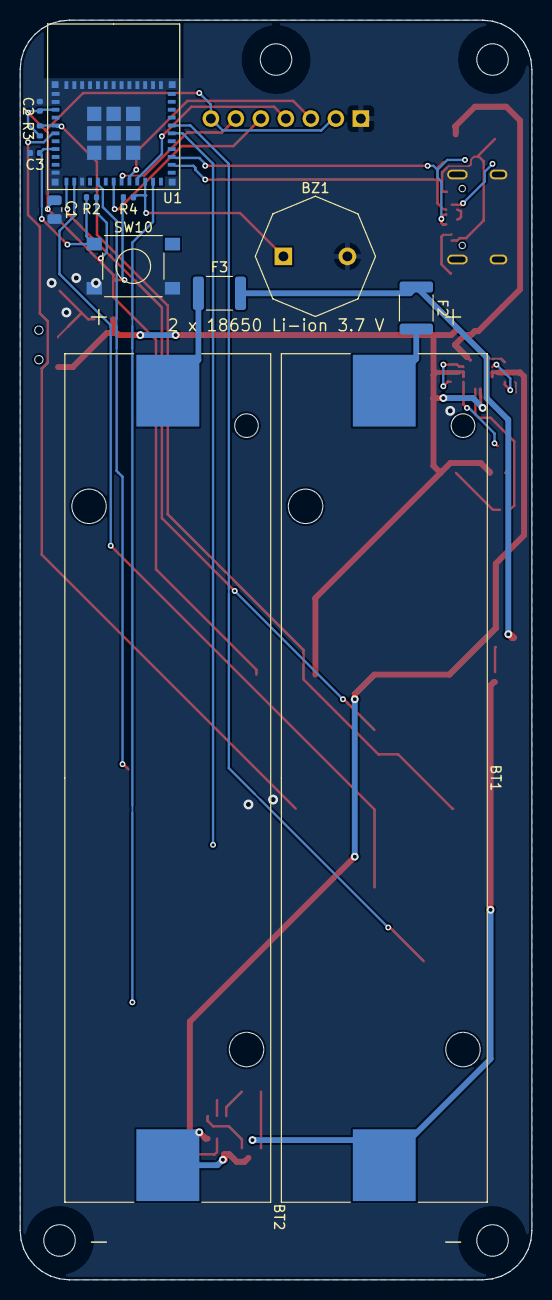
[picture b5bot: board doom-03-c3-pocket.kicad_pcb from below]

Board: 2 copper layers, 52.0 x 128.0 mm, 60 parts (13 on the bottom side), 42 nets.

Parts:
BT1, BT2: 1042; BatteryHolder_Keystone_1042_1x18650
BZ1: GPC12075YB-5V4000; Buzzer_D12.0mm_H7.5mm_P6.50mm
C1: 10uF; C_0805_2012Metric
C2, C6: 100nF; C_0402_1005Metric
C3, C7, C8: 1uF; C_0402_1005Metric
D1: tvs 5V; D_SOD-123
DS1: MSP1308 1.3in 240x240 IPS SPI module (ST7789); TFT_1.3in_ST7789_Socket_1x07_P2.54mm
F1: PTC 750mA; Fuse_1206_3216Metric
F2, F3: PTC 2000mA; Fuse_1812_4532Metric
H1, H2, H3, H4: MountingHole_3.2mm_M3
J1: USB4105-GF-A; USB_C_Receptacle_USB2.0_16P
Q1: AO3401A; SOT-23
Q2: FS8205A; TSSOP-8_4.4x2.93mm_P0.65mm
R1: 1Mohm; R_0402_1005Metric
R2, R3, R4: 10kohm; R_0402_1005Metric
R5, R6: 5.1kohm; R_0402_1005Metric
R7: 100kohm; R_0402_1005Metric
R9: 100ohm; R_0402_1005Metric
R10: 1kohm; R_0402_1005Metric
SW1, SW2, SW3, SW4, SW5, SW6, SW7, SW8: TS-1187A-B-A-B; SW_Tactile_SPST_5.1x5.1mm_SMD
SW9: MSK12C02; SW_Slide_SPDT_Shouhan_MSK12C02
SW10: PTS645SM43SMTR92 LFS; SW_Tactile_SPST_6x6mm_SMD
U1: ESP32-C3-MINI-1-H4; ESP32-C3-MINI-1_module_13.2x16.6mm_LGA_53_pads
U2: BQ24075RGTR; QFN-16-1EP_3x3mm_P0.5mm_EP1.68x1.68mm
U3: DW01A; SOT-6_1.6x2.9mm_P0.95mm
U4: AP2112K-3.3TRG1; SOT-23-5
U5: USBLC6-2SC6; SOT-23-6
cBat: 4.7uF; C_0805_2012Metric
cIn: 1uF; C_0603_1608Metric
cSys: 4.7uF; C_0805_2012Metric
ledChg: red; LED_0603_1608Metric
ledPg: green; LED_0603_1608Metric
logo: Logo_PCBKit_pcbkit.io
rChg: 1.5kohm; R_0402_1005Metric
rIlim: 1.18kohm; R_0402_1005Metric
rIset: 1.13kohm; R_0402_1005Metric
rPg: 1.5kohm; R_0402_1005Metric
rTs: 10kohm; R_0402_1005Metric
tpBat: TestPoint_Round_D1.5mm
tpGnd: TestPoint_Round_D1.5mm
tpSys: TestPoint_Round_D1.5mm
tpV3: TestPoint_Round_D1.5mm

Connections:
BAT: Q1.2 (S), R9.1 (a), U2.2 (BAT), U2.3 (BAT), cBat.1 (a), tpBat.1
BAT_IN: F2.2 (b), F3.2 (b), Q1.3 (D)
BUZZ: BZ1.1 (A), R4.1 (a), U1.22 (IO8)
CELL1_P: BT1.2 (C2), F2.1 (a)
CELL2_P: BT2.2 (C2), F3.1 (a)
CELL_N: BT1.1 (C1), BT2.1 (C1), C6.2 (b), Q2.2 (S1), Q2.3 (S1), R7.1 (a), U3.6 (GND)
CHG_LED: ledChg.1 (K), rChg.1 (a)
CHG_N: U2.9 (nCHG), rChg.2 (b)
DN: J1.A7 (DN), J1.B7 (DN), U1.26 (IO18), U5.3 (IO2)
DOWN: SW2.1 (a), U1.13 (IO1)
DP: J1.A6 (DP), J1.B6 (DP), U1.27 (IO19), U5.1 (IO1)
EN: C3.1 (a), R2.2 (b), SW10.1 (a), U1.8 (EN)
FIRE: SW5.1 (a), U1.16 (IO10)
GND: BZ1.2 (B), C1.2 (b), C2.2 (b), C3.2 (b), C7.2 (b), C8.2 (b), D1.2 (A), DS1.1 (GND), J1.A1 (GND), J1.A12, J1.B1 (GND), J1.B12, J1.S1 (SHIELD), Q2.6 (S2), Q2.7 (S2), R1.2 (b), R5.2 (b), R6.2 (b), R10.2 (b), SW1.2 (b), SW2.2 (b), SW3.2 (b), SW4.2 (b), SW5.2 (b), SW6.2 (b), SW7.2 (b), SW8.2 (b), SW9.4 (SHELL), SW10.2 (b), U1.1 (GND), U1.2 (GND), U1.11 (GND), U1.14 (GND), U1.36 (GND), U1.37 (GND), U1.38 (GND), U1.39 (GND), U1.40 (GND), U1.41 (GND), U1.42 (GND), U1.43 (GND), U1.44 (GND), U1.45 (GND), U1.46 (GND), U1.47 (GND), U1.48 (GND), U1.49 (GND), U1.50 (GND), U1.51 (GND), U1.52 (GND), U1.53 (GND), U2.4 (nCE), U2.5 (EN2), U2.8 (VSS), U2.14 (TMR), U2.15 (SYSOFF), U2.17 (VSS), U4.2 (GND), U5.2 (GND), cBat.2 (b), cIn.2 (b), cSys.2 (b), rIlim.2 (b), rIset.2 (b), rTs.2 (b), tpGnd.1
ILIM: U2.12 (ILIM), rIlim.1 (a)
ISET: U2.16 (ISET), rIset.1 (a)
LCD_DC: DS1.6 (DC), U1.19 (IO5)
LCD_RST: DS1.5 (RES), U1.18 (IO4)
LDO_EN: R1.1 (a), SW9.2 (COM), U4.3 (EN)
LEFT: R3.2 (b), SW3.1 (a), U1.5 (IO2)
MENU: SW8.1 (a), U1.23 (IO9)
MOSI: DS1.4 (SDA), U1.21 (IO7)
unnamed: C6.1 (a), R9.2 (b), U3.5 (VCC)
unnamed: Q2.4 (G1), U3.1 (OD)
unnamed: Q2.5 (G2), U3.3 (OC)
unnamed: R10.1 (a), U3.2 (CS)
PG_LED: ledPg.1 (K), rPg.1 (a)
PG_N: U2.7 (nPGOOD), rPg.2 (b)
RIGHT: SW4.1 (a), U1.6 (IO3)
SCK: DS1.3 (SCL), U1.20 (IO6)
STRAFE: SW7.1 (a), U1.31 (TXD0)
SYS: C7.1 (a), SW9.1 (A), U2.6 (EN1), U2.10 (OUT), U2.11 (OUT), U4.1 (VIN), cSys.1 (a), ledChg.2 (A), ledPg.2 (A), tpSys.1
TS: U2.1 (TS), rTs.1 (a)
U3Support/DRAIN: Q2.1 (D12), Q2.8 (D12)
UP: SW1.1 (a), U1.12 (IO0)
USE: SW6.1 (a), U1.30 (RXD0)
V3: C1.1 (a), C2.1 (a), C8.1 (a), DS1.2 (VCC), DS1.7 (BLK), R2.1 (a), R3.1 (a), R4.2 (b), U1.3 (P3V3), U4.5 (VOUT), tpV3.1
VBUS: D1.1 (K), F1.2 (b), U2.13 (IN), U5.5 (VBUS), cIn.1 (a)
reversed/gate: Q1.1 (G), R7.2 (b)
usb/power/cc1: J1.A5 (CC1), R5.1 (a)
usb/power/cc2: J1.B5 (CC2), R6.1 (a)
usb/power/vbusIn: F1.1 (a), J1.A4 (VBUS), J1.A9, J1.B4 (VBUS), J1.B9
